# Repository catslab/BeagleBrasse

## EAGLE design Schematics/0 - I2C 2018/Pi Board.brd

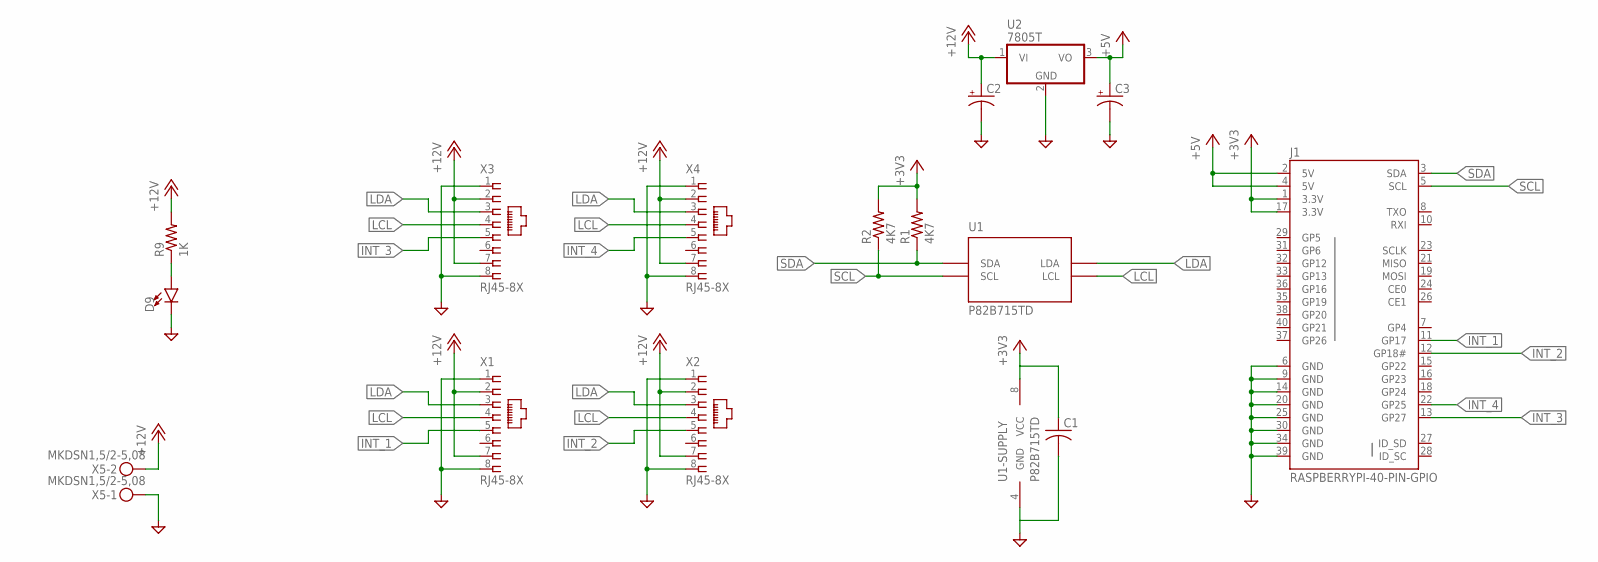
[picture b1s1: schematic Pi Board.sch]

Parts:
C1: C-USC0805; C0805
C2, C3: CPOL-USC; PANASONIC_C
D9: LED3MM; LED_3MM
J1: RASPBERRYPI-40-PIN-GPIO; 2X20-SHROUDED
R1, R2: 4K7; R0805
R9: 1K; R0805
U1: P82B715TD; SOIC-8
U2: 7805T; TO220H
X1, X2, X3, X4: RJ45-8X; RJ45-NO-SHIELD
X5: MKDSN1,5/2-5,08

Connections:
+3V3: C1.1, J1.1 (3.3V), J1.17 (3.3V), R1.2, R2.2, U1.8 (VCC)
+5V: C3.+, J1.2 (5V), J1.4 (5V), U2.3 (VO)
+12VBUS: C2.+, R9.2, U2.1 (VI), X1.2, X1.7, X2.2, X2.7, X3.2, X3.7, X4.2, X4.7, X5.2
DGND: C1.2, C2.-, C3.-, D9.K (C), J1.6 (GND), J1.9 (GND), J1.14 (GND), J1.20 (GND), J1.25 (GND), J1.30 (GND), J1.34 (GND), J1.39 (GND), U1.4 (GND), U2.2 (GND), X1.1, X1.8, X2.1, X2.8, X3.1, X3.8, X4.1, X4.8, X5.1
INT_1: J1.11 (GP17), X1.5
INT_2: J1.12 (GP18#), X2.5
INT_3: J1.13 (GP27), X3.5
INT_4: J1.22 (GP25), X4.5
LCL: U1.2 (LCL), X1.4, X2.4, X3.4, X4.4
LDA: U1.7 (LDA), X1.3, X2.3, X3.3, X4.3
unnamed: D9.A, R9.1
SCL: J1.5 (SCL), R2.1, U1.3 (SCL)
SDA: J1.3 (SDA), R1.1, U1.6 (SDA)

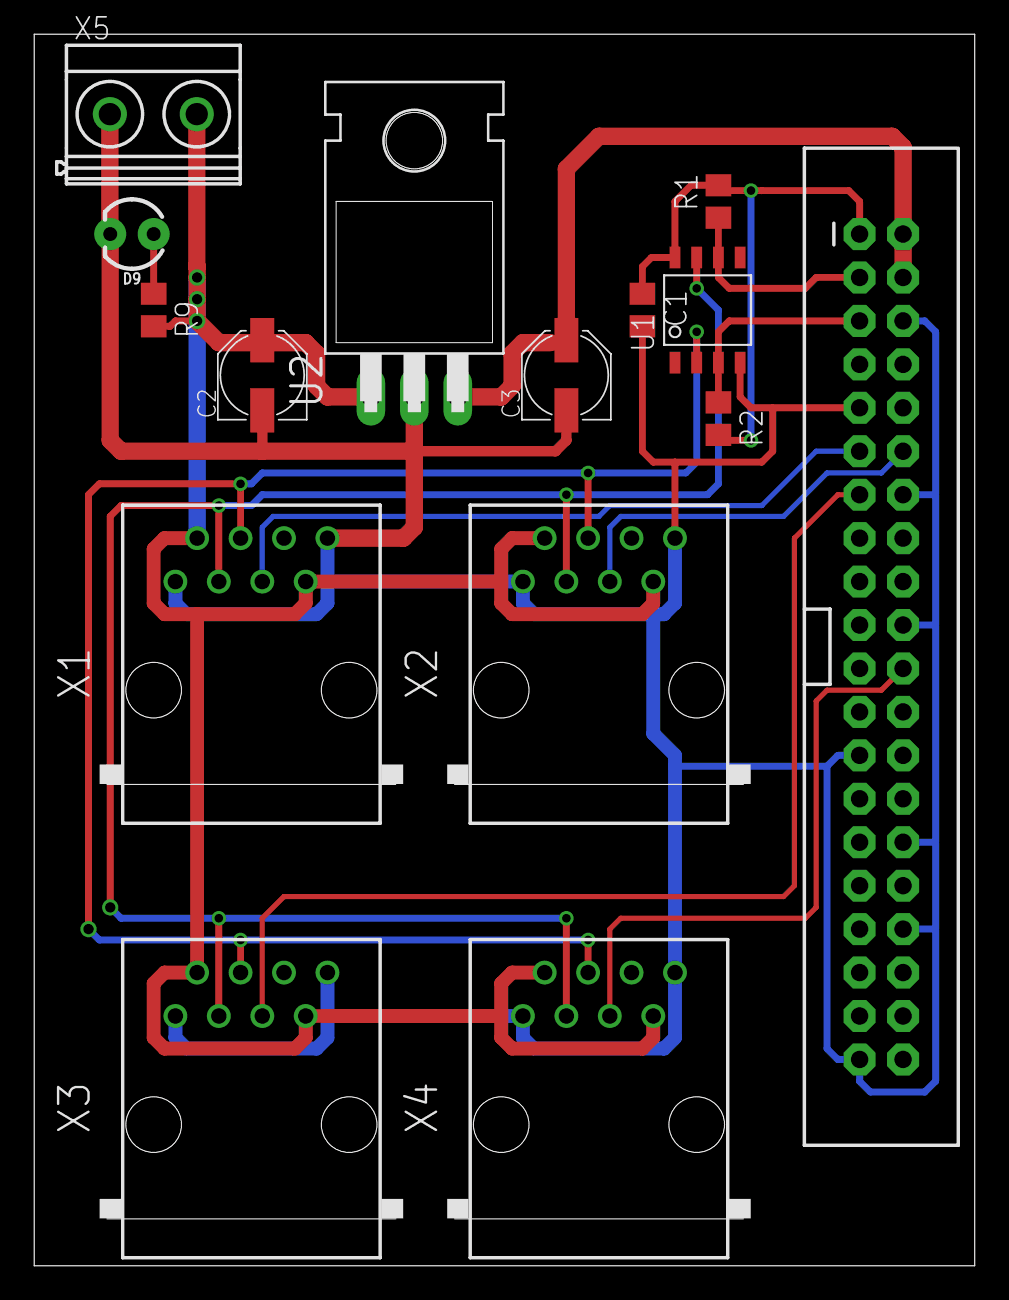
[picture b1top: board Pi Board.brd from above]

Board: 2 copper layers, 55.0 x 72.0 mm, 15 parts (0 on the bottom side), 13 nets.

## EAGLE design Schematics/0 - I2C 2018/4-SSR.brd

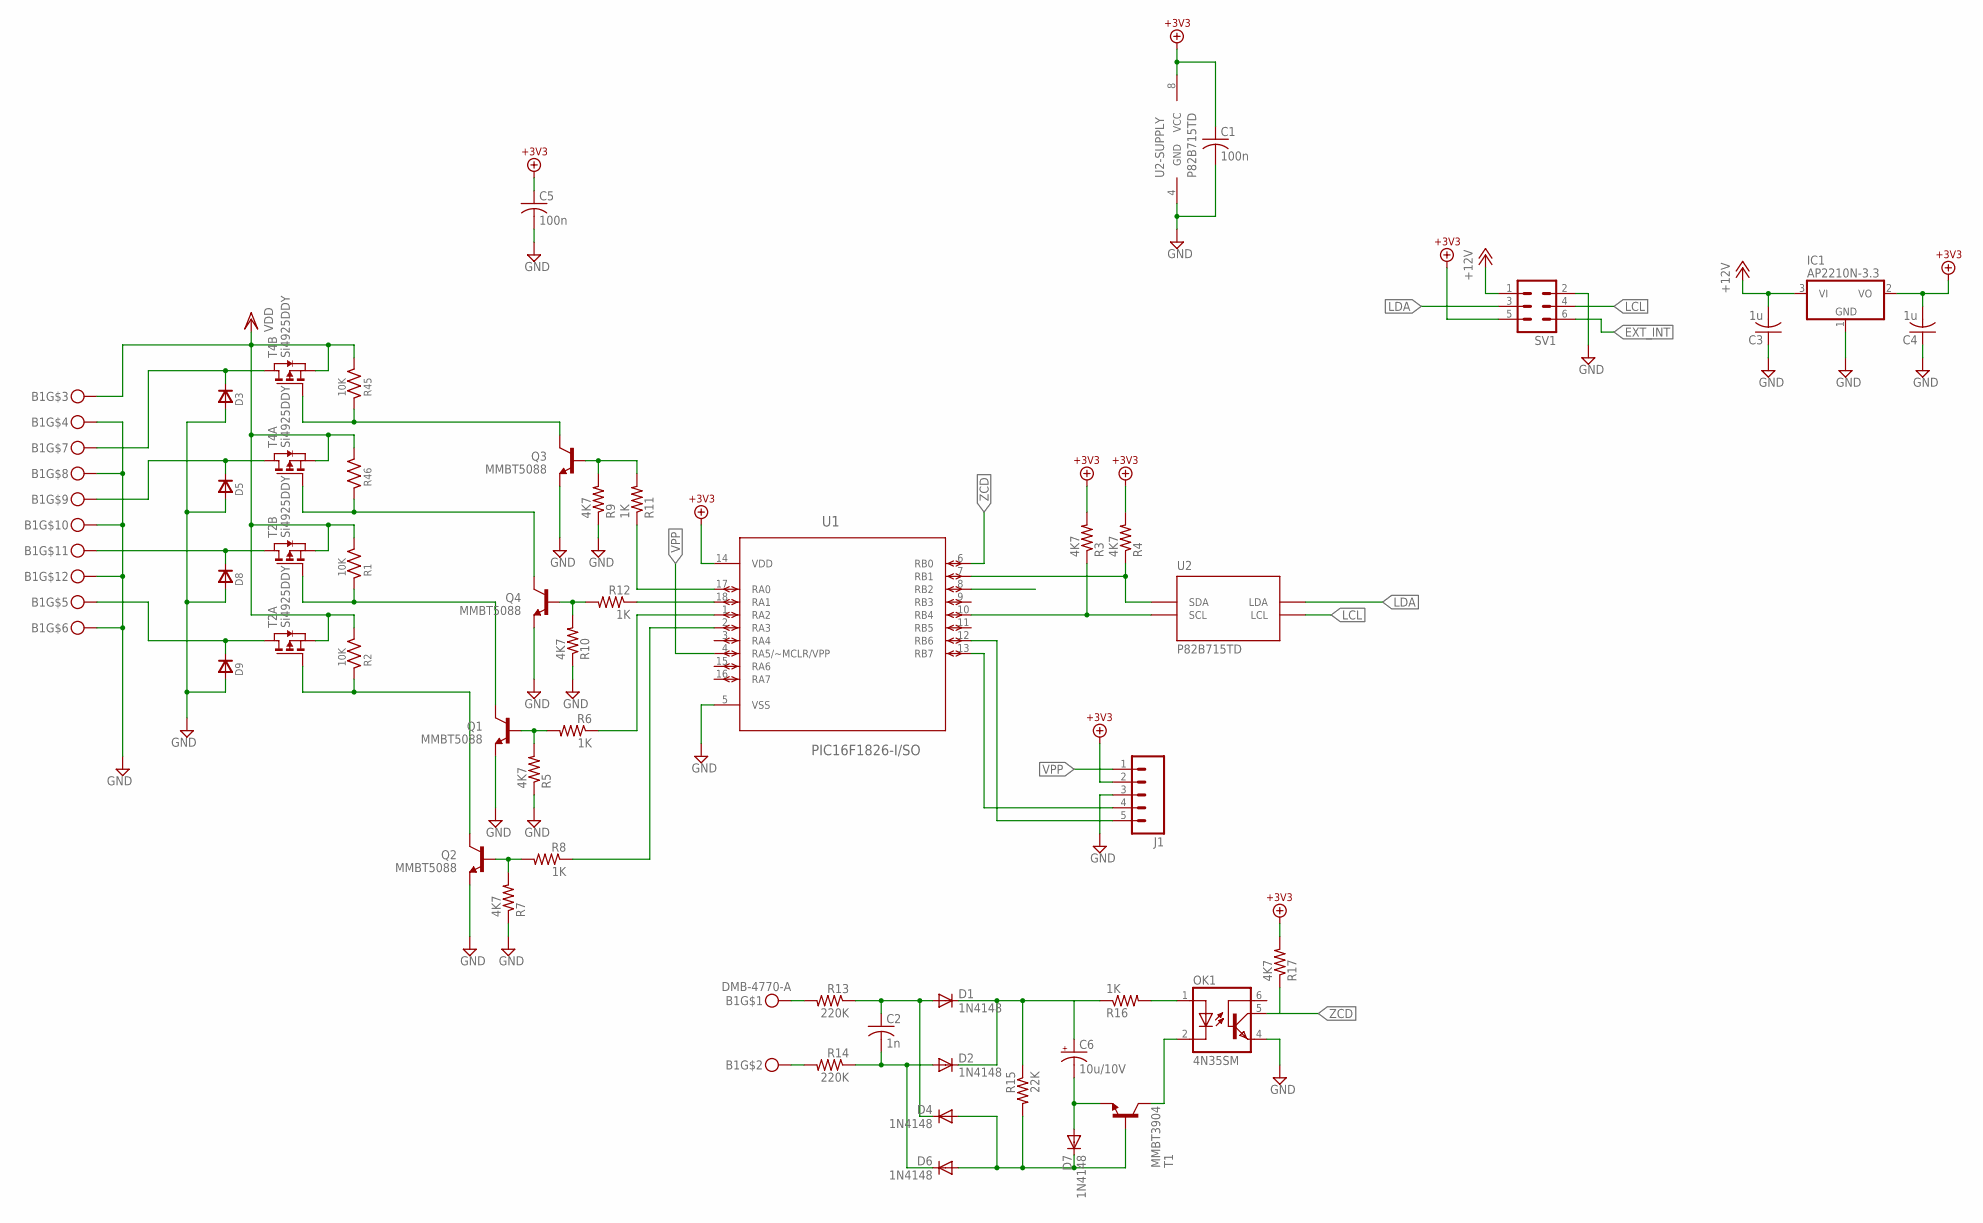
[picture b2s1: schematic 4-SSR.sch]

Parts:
B1: DMB-4770-A; DMB-4770-A-PKG
C1, C5: 100n; C0805
C2: 1n; C1808
C3, C4: 1u; C0805
C6: 10u/10V; PANASONIC_B
D1, D2, D4, D6, D7: 1N4148; SOD80C
D3, D5, D8, D9: DSMA
IC1: AP2210N-3.3; SOT23
J1: M05PTH; 1X05
OK1: 4N35SM; DIL6-SMD
Q1, Q2, Q3, Q4: MMBT5088; SOT23-3
R1, R2, R45: 10K; R0805
R3, R4, R5, R7, R9, R10, R17: 4K7; R0805
R6, R8, R11, R12, R16: 1K; R0805
R13, R14: 220K; R0805
R15: 22K; R0805
R46: RU0805; R0805
SV1: ML6
T1: MMBT3904; SOT23-BEC
T2, T4: Si4925DDY; SO8
U1: PIC16F1826-I/SO; SOIC127P1030X175-18N
U2: P82B715TD; SOIC-8

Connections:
+3V3: C1.1, C4.2, C5.1, IC1.2 (VO), J1.2, R3.2, R4.2, R17.2, SV1.5, U1.14 (VDD), U2.8 (VCC)
+12VBUS: C3.2, IC1.3 (VI), SV1.1
EXT_INT: SV1.6
GND: B1.P$4, B1.P$6, B1.P$8, B1.P$10, B1.P$12, C1.2, C3.1, C4.1, C5.2, D3.A, D5.A, D8.A, D9.A, IC1.1 (GND), J1.3, OK1.4 (EMI), Q1.2 (E), Q2.2 (E), Q3.2 (E), Q4.2 (E), R5.1, R7.1, R9.1, R10.1, SV1.2, U1.5 (VSS), U2.4 (GND)
LCL: SV1.4, U2.2 (LCL)
LDA: SV1.3, U2.7 (LDA)
unnamed: Q1.3 (C), R1.1, T2.4 (G)
unnamed: B1.P$11, D8.C, T2.5 (D), T2.6 (D)
unnamed: Q2.3 (C), R2.1, T2.2 (G)
unnamed: B1.P$5, D9.C, T2.7 (D), T2.8 (D)
unnamed: J1.4, U1.13 (RB7)
unnamed: J1.5, U1.12 (RB6)
unnamed: R12.1, U1.18 (RA1)
unnamed: Q4.3 (C), R46.1, T4.2 (G)
unnamed: Q3.1 (B), R9.2, R11.2
unnamed: R11.1, U1.17 (RA0)
unnamed: Q1.1 (B), R5.2, R6.2
unnamed: Q4.1 (B), R10.2, R12.2
unnamed: B1.P$1, R13.2
unnamed: B1.P$2, R14.2
unnamed: C2.1, D1.A, D4.C, R13.1
unnamed: C2.2, D2.A, D6.C, R14.1
unnamed: C6.+, D1.C, D2.C, R15.1, R16.1
unnamed: C6.-, D7.A, T1.E
unnamed: OK1.1 (A), R16.2
unnamed: D4.A, D6.A, D7.C, R15.2, T1.B
unnamed: OK1.2 (C), T1.C
unnamed: R6.1, U1.1 (RA2)
unnamed: Q2.1 (B), R7.2, R8.2
unnamed: R8.1, U1.2 (RA3)
unnamed: R3.1, U1.10 (RB4), U2.3 (SCL)
unnamed: R4.1, U1.7 (RB1), U2.6 (SDA)
unnamed: Q3.3 (C), R45.1, T4.4 (G)
unnamed: B1.P$7, D3.C, T4.5 (D), T4.6 (D)
unnamed: B1.P$9, D5.C, T4.7 (D), T4.8 (D)
VDD: B1.P$3, R1.2, R2.2, R45.2, R46.2, T2.1 (S), T2.3 (S), T4.1 (S), T4.3 (S)
VPP: J1.1, U1.4 (RA5/~MCLR/VPP)
ZCD: OK1.5 (COL), R17.1, U1.6 (RB0)

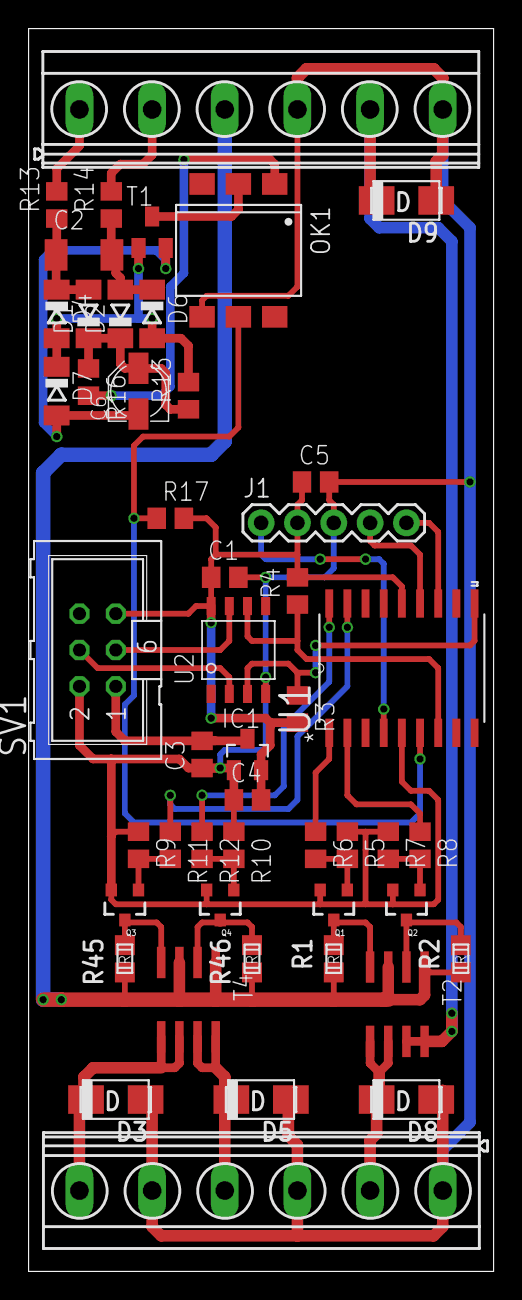
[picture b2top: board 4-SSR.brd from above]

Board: 2 copper layers, 32.5 x 86.9 mm, 48 parts (0 on the bottom side), 37 nets.

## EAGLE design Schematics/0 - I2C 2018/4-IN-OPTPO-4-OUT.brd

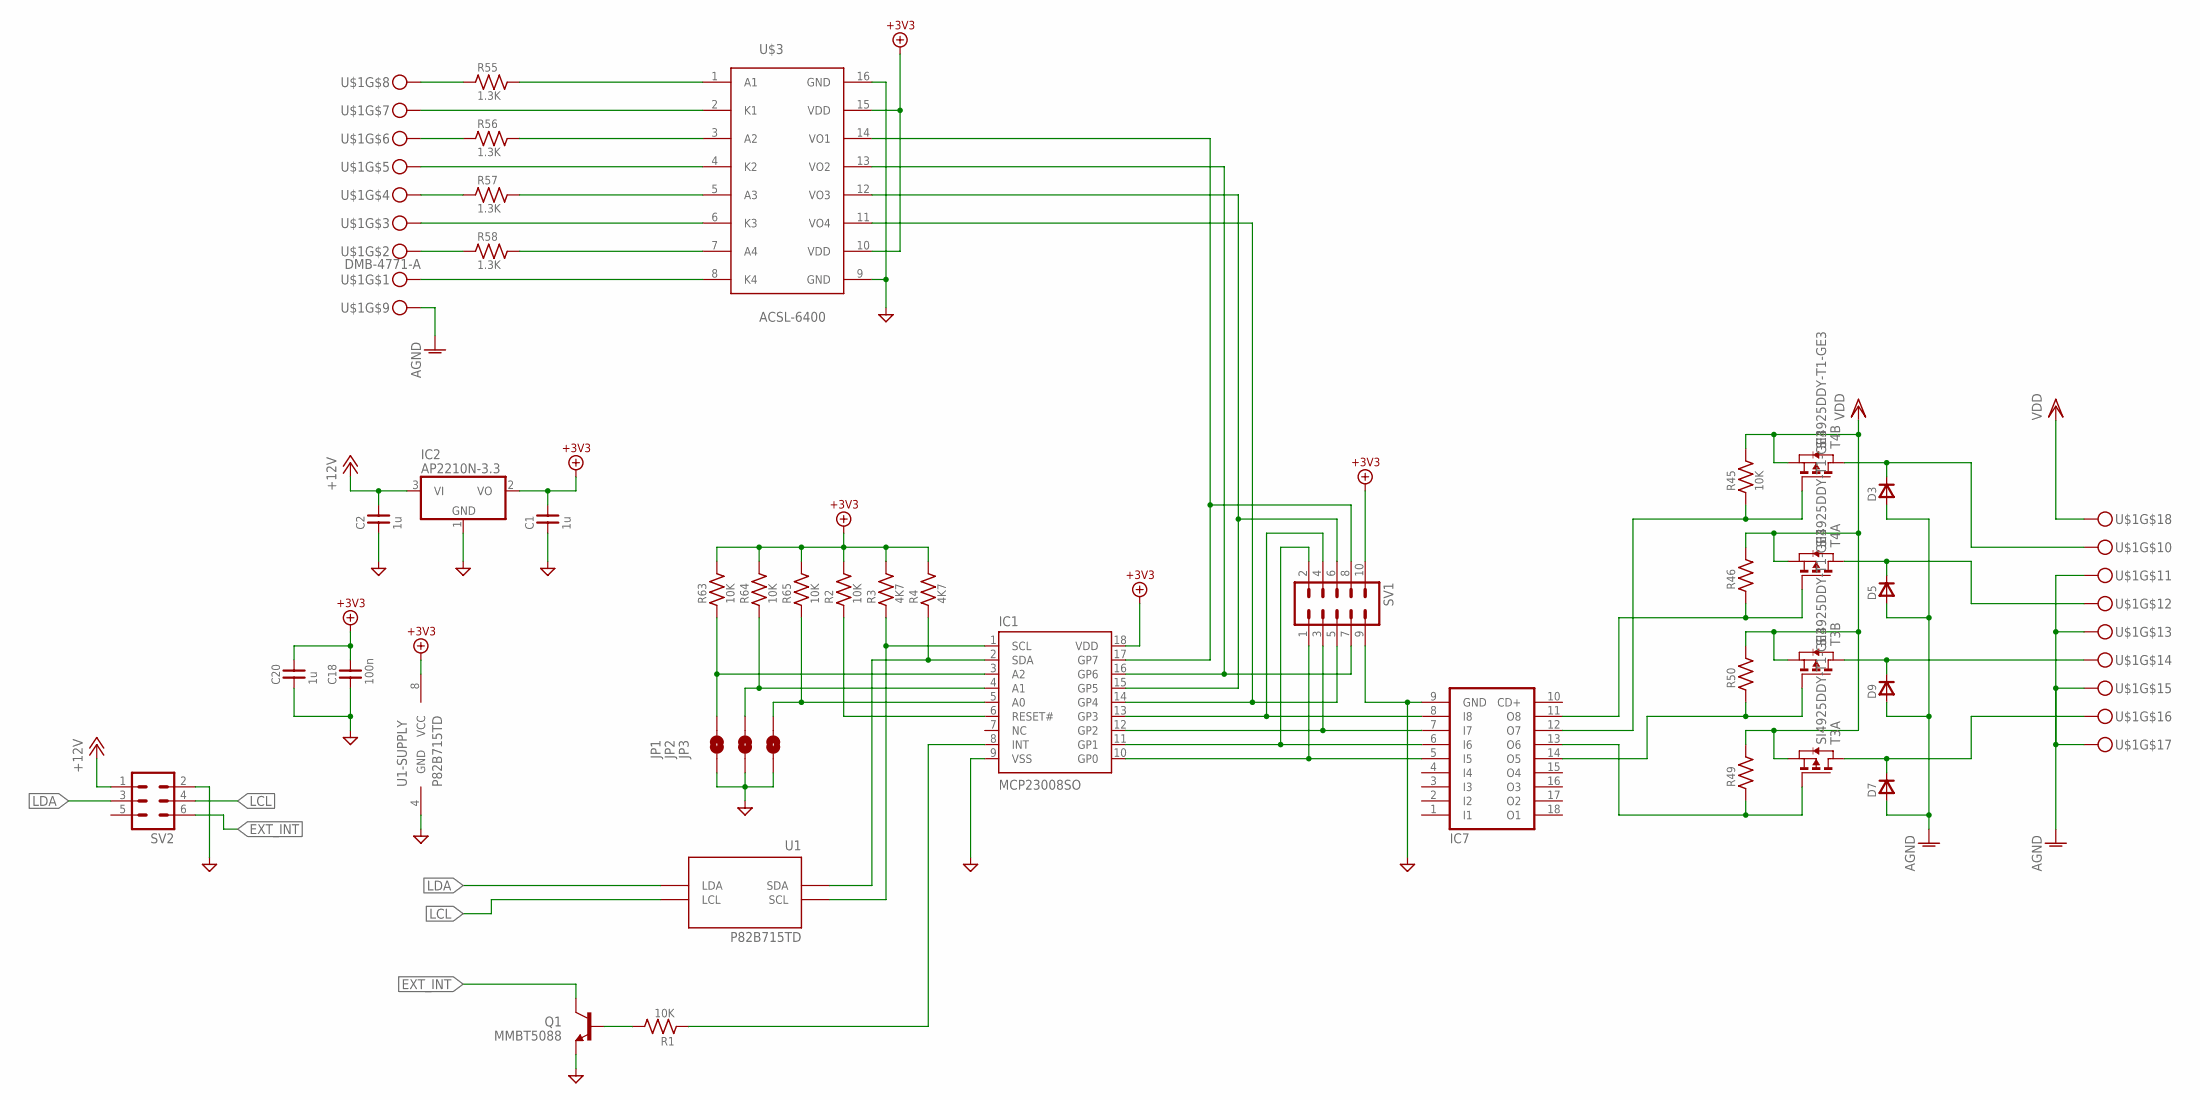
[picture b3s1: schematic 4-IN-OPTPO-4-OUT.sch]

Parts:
C1, C2, C20: 1u; C0805
C18: 100n; C0805
D3, D5, D7, D9: DSMA
IC1: MCP23008SO; SO-18W
IC2: AP2210N-3.3; SOT23
IC7: ULN2803A; SO18W
JP1, JP2, JP3: JUMPER-PAD-2-NOYES_SILK; PAD-JUMPER-2-NO_YES_SILK
Q1: MMBT5088; SOT23-3
R1, R2, R45, R63, R64, R65: 10K; R0805
R3, R4: 4K7; R0805
R46, R49, R50: RU0805; R0805
R55, R56, R57, R58: 1.3K; R0805
SV1: ML10
SV2: ML6
T3, T4: SI4925DDY-T1-GE3; SO8
U1: P82B715TD; SOIC-8
U$1: DMB-4771-A; DMB-4771-A-PKG
U$3: ACSL-6400; SO16

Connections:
+3V3: C1.2, C18.2, C20.2, IC1.18 (VDD), IC2.2 (VO), R2.2, R3.2, R4.2, R63.2, R64.2, R65.2, SV1.10, U1.8 (VCC), U$3.10 (VDD), U$3.15 (VDD)
+12VBUS: C2.2, IC2.3 (VI), SV2.1
AGND: D3.A, D5.A, D7.A, D9.A, U$1.P$9, U$1.P$11, U$1.P$13, U$1.P$15, U$1.P$17
DGND: C1.1, C2.1, C18.1, C20.1, IC1.9 (VSS), IC2.1 (GND), IC7.9 (GND), JP1.1, JP2.1, JP3.1, Q1.2 (E), SV1.9, SV2.2, U1.4 (GND), U$3.9 (GND), U$3.16 (GND)
EXT_INT: Q1.3 (C), SV2.6
LCL: SV2.4, U1.2 (LCL)
LDA: SV2.3, U1.7 (LDA)
unnamed: R55.1, U$1.P$8
unnamed: R56.1, U$1.P$6
unnamed: R57.1, U$1.P$4
unnamed: R58.1, U$1.P$2
unnamed: IC1.13 (GP3), IC7.8 (I8), SV1.4
unnamed: IC1.12 (GP2), IC7.7 (I7), SV1.3
unnamed: IC1.11 (GP1), IC7.6 (I6), SV1.2
unnamed: IC1.10 (GP0), IC7.5 (I5), SV1.1
unnamed: IC1.1 (SCL), R3.1, U1.3 (SCL)
unnamed: IC1.2 (SDA), R4.1, U1.6 (SDA)
unnamed: IC1.8 (INT), R1.1
unnamed: Q1.1 (B), R1.2
unnamed: IC1.6 (RESET#), R2.1
unnamed: IC1.16 (GP6), SV1.7, U$3.13 (VO2)
unnamed: U$1.P$7, U$3.2 (K1)
unnamed: U$1.P$5, U$3.4 (K2)
unnamed: U$1.P$3, U$3.6 (K3)
unnamed: U$1.P$1, U$3.8 (K4)
unnamed: IC7.12 (O7), R45.1, T4.4 (G)
unnamed: IC7.11 (O8), R46.1, T4.2 (G)
unnamed: IC7.13 (O6), R49.1, T3.2 (G)
unnamed: IC7.14 (O5), R50.1, T3.4 (G)
unnamed: D3.C, T4.5 (D), T4.6 (D), U$1.P$10
unnamed: D5.C, T4.7 (D), T4.8 (D), U$1.P$12
unnamed: D7.C, T3.7 (D), T3.8 (D), U$1.P$16
unnamed: D9.C, T3.5 (D), T3.6 (D), U$1.P$14
unnamed: R55.2, U$3.1 (A1)
unnamed: R56.2, U$3.3 (A2)
unnamed: R57.2, U$3.5 (A3)
unnamed: R58.2, U$3.7 (A4)
unnamed: IC1.17 (GP7), SV1.8, U$3.14 (VO1)
unnamed: IC1.15 (GP5), SV1.6, U$3.12 (VO3)
unnamed: IC1.14 (GP4), SV1.5, U$3.11 (VO4)
unnamed: IC1.5 (A0), JP3.2, R65.1
unnamed: IC1.4 (A1), JP2.2, R64.1
unnamed: IC1.3 (A2), JP1.2, R63.1
VDD: R45.2, R46.2, R49.2, R50.2, T3.1 (S), T3.3 (S), T4.1 (S), T4.3 (S), U$1.P$18

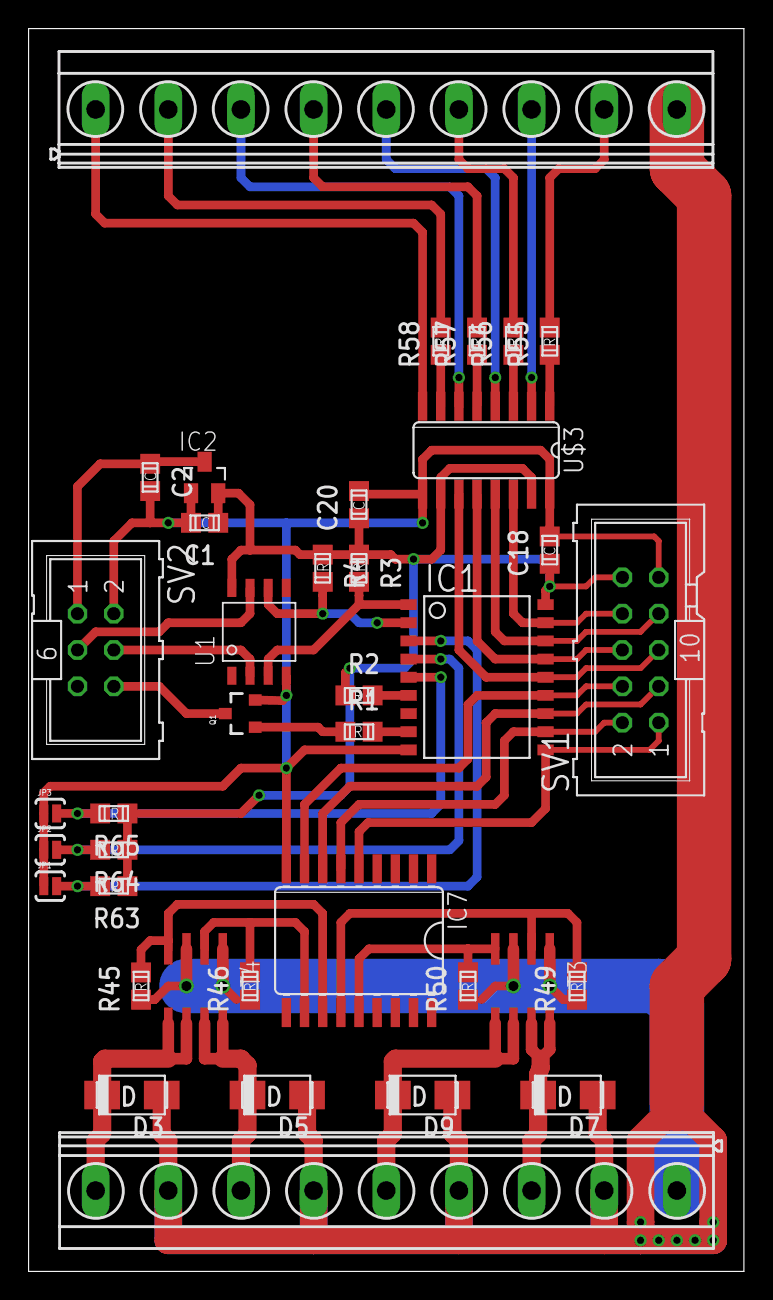
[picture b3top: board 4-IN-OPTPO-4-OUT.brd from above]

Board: 2 copper layers, 50.0 x 86.9 mm, 37 parts (0 on the bottom side), 44 nets.

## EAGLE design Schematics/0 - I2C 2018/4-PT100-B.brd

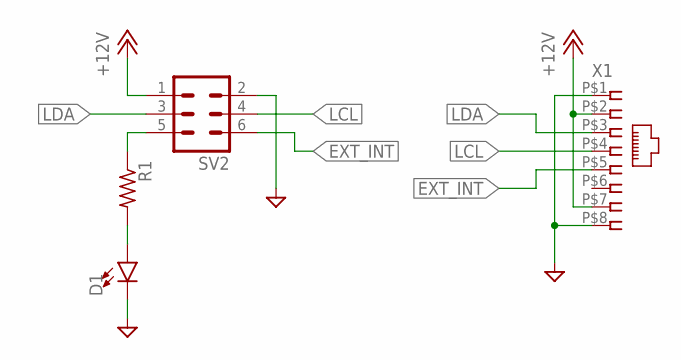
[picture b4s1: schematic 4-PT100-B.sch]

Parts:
D1: LED3MM; LED_3MM
R1: R-US_R0805; R0805
SV2: ML6
X1: RJ45; RJ45-VERT

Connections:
+12VBUS: SV2.1, X1.P$2 (2), X1.P$7 (7)
DGND: D1.K (C), SV2.2, X1.P$1 (1), X1.P$8 (8)
EXT_INT: SV2.6, X1.P$5 (5)
LCL: SV2.4, X1.P$4 (4)
LDA: SV2.3, X1.P$3 (3)
unnamed: D1.A, R1.2
unnamed: R1.1, SV2.5

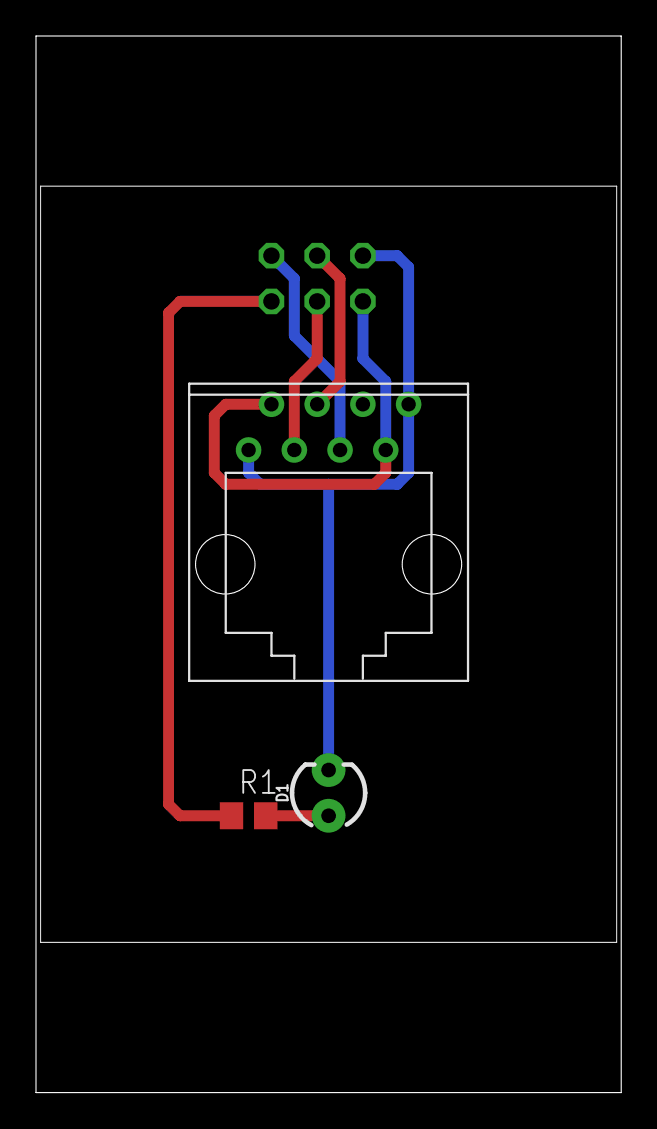
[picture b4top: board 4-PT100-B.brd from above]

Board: 2 copper layers, 32.5 x 58.7 mm, 4 parts (1 on the bottom side), 7 nets.

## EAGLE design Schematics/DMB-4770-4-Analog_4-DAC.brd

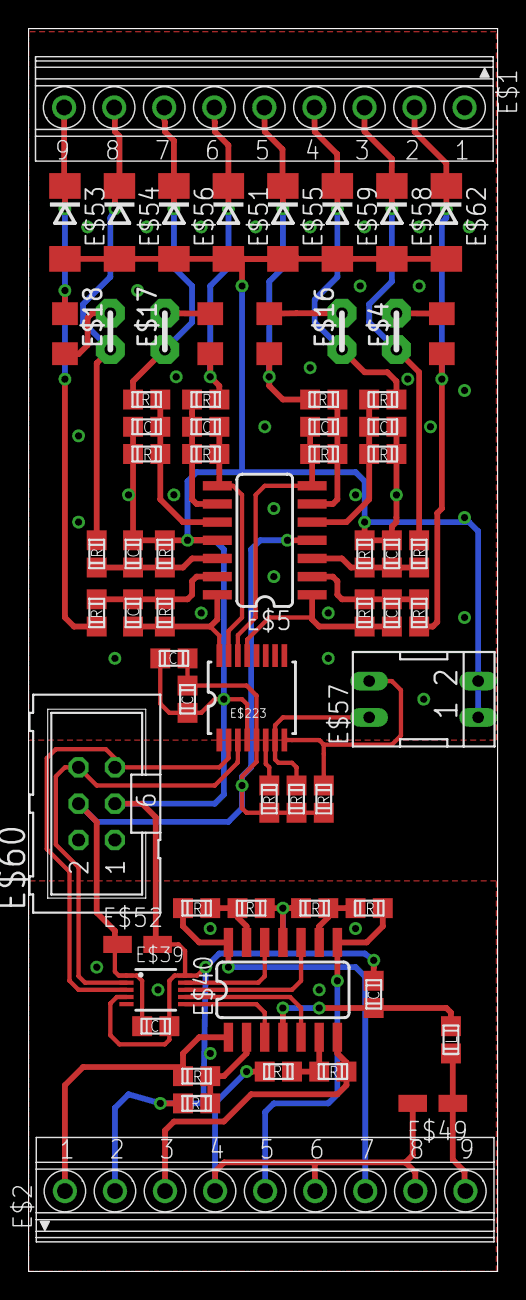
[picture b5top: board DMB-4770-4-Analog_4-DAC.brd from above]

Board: 2 copper layers, 32.8 x 86.9 mm, 66 parts (0 on the bottom side), 45 nets.

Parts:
E$1, E$2: 1751316
E$3, E$10, E$13, E$22, E$24, E$26, E$30, E$32, E$36, E$37, E$38: 100n; C0805
E$4, E$16, E$17, E$18: J01N
E$5: LMV344; SOIC-14
E$6, E$9, E$21, E$23, E$25, E$29, E$31, E$35: 25.5K; R0805
E$7, E$8, E$19, E$66: 500; 1206
E$11, E$12, E$14, E$15, E$27, E$28, E$33, E$34: 102K; R0805
E$39: MCP4728; MSOP10
E$40: OPA4171; SOIC-14
E$41, E$43, E$45, E$46: 82.5K; R0805
E$42, E$44, E$47, E$48: 330K; R0805
E$49, E$52: 10u; CT3216
E$50: 1u; C0805
E$51, E$53, E$55, E$56, E$58, E$59, E$62: 1SMB30AT3G; DO214AA
E$54: DO214AA
E$57: EPG-02
E$60: ML6
E$61: 10uH; L0805
E$223: ADC128D818; TSSOP16
E$224, E$225, E$226: 10K; R0805

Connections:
3V3: E$3.2, E$5.4, E$37.1, E$39.1, E$50.1, E$52.+, E$60.4, E$223.5, E$224.2, E$225.2, E$226.2
GND: E$2.2, E$2.4, E$2.6, E$2.8, E$3.1, E$5.11, E$9.2, E$13.2, E$21.1, E$22.1, E$29.1, E$30.1, E$31.2, E$32.2, E$37.2, E$38.1, E$39.4, E$39.10, E$40.11, E$41.2, E$43.2, E$45.1, E$46.1, E$49.-, E$50.2, E$51.A, E$52.-, E$53.A, E$54.A, E$55.A, E$56.A, E$57.1, E$57.2, E$58.A, E$59.A, E$60.3, E$62.A, E$223.4
IN1+: E$1.8, E$18.1, E$34.2, E$54.C
IN1-: E$1.9, E$33.2, E$53.C, E$66.2
IN2+: E$1.7, E$17.1, E$27.2, E$56.C
IN2-: E$1.6, E$19.2, E$28.2, E$51.C
IN3+: E$1.4, E$15.2, E$16.1, E$59.C
IN3-: E$1.5, E$8.2, E$14.2, E$55.C
IN4+: E$1.3, E$4.1, E$11.2, E$58.C
IN4-: E$1.2, E$7.2, E$12.2, E$62.C
S$8: E$39.3, E$60.5, E$223.2
S$9: E$2.9, E$49.+, E$61.1
S$10: E$4.2, E$7.1
S$11: E$40.6, E$43.1, E$44.1
S$13: E$5.2, E$6.1, E$10.1, E$12.1
S$14: E$5.6, E$14.1, E$23.2, E$24.2
S$15: E$18.2, E$66.1
S$16: E$5.5, E$9.1, E$13.1, E$15.1
S$20: E$17.2, E$19.1
S$21: E$8.1, E$16.2
S$23: E$5.3, E$11.1, E$21.2, E$22.2
S$25: E$5.9, E$25.1, E$26.1, E$28.1
S$28: E$5.12, E$31.1, E$32.1, E$34.1
S$29: E$5.10, E$27.1, E$29.2, E$30.2
S$31: E$39.6, E$40.3
S$32: E$39.7, E$40.5
S$33: E$39.9, E$40.12
S$34: E$39.8, E$40.10
S$35: E$40.2, E$41.1, E$42.2
S$38: E$2.1, E$40.1, E$42.1
S$39: E$2.3, E$40.7, E$44.2
S$40: E$40.13, E$45.2, E$48.2
S$41: E$40.9, E$46.2, E$47.1
S$42: E$2.7, E$40.14, E$48.1
S$47: E$5.8, E$25.2, E$26.2, E$223.15
S$48: E$5.7, E$23.1, E$24.1, E$223.14
S$49: E$5.14, E$35.1, E$36.1, E$223.16
S$50: E$5.1, E$6.2, E$10.2, E$223.13
S$55: E$5.13, E$33.1, E$35.2, E$36.2
S$59: E$2.5, E$40.8, E$47.2
S$231: E$223.6, E$226.1
S$235: E$57.4, E$223.7, E$225.1
S$236: E$57.3, E$223.8, E$224.1
SCL: E$39.2, E$60.6, E$223.3
VCC: E$38.2, E$40.4, E$61.2

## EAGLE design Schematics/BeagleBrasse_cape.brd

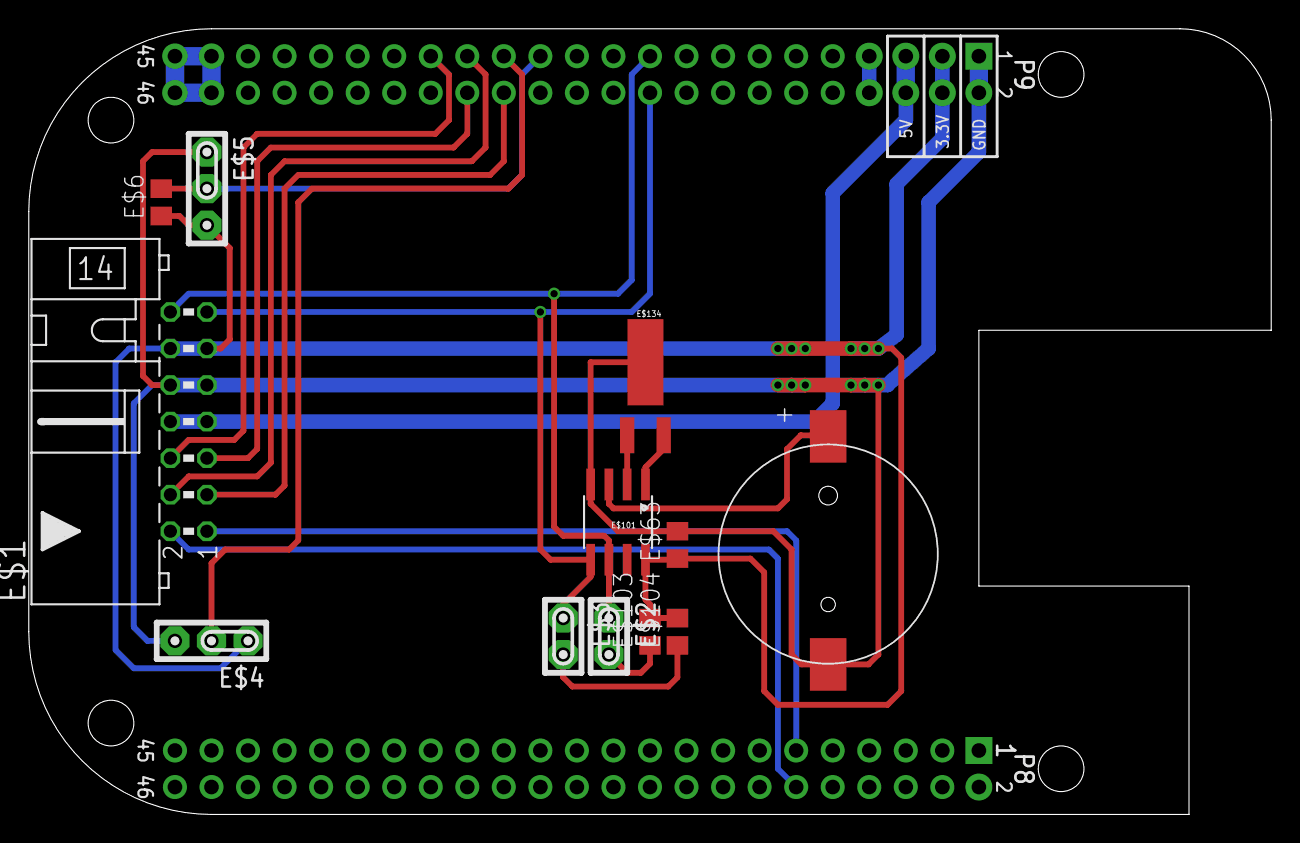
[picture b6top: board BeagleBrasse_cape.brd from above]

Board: 2 copper layers, 86.4 x 54.6 mm, 13 parts (0 on the bottom side), 20 nets.

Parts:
E$1: ML14L
E$2, E$3: JP02N
E$4, E$5: JP03N
E$6, E$103, E$104: 4.7K; C0805
E$63: 0.1; C0805
E$101: DS1338; SOIC8
E$102: BC501SM
E$134: 32.768; CRYSTAL-32KHZ-SMD
U$1: BEAGLE_BONE_BLACK_CAPE

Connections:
S$1: E$1.7, E$1.8, U$1.P9.5, U$1.P9.6
S$2: E$101.2, E$134.X1
S$3: E$101.1, E$134.X2
S$4: E$101.3, E$102.P$2
S$5: E$1.14, E$2.1, E$101.6, U$1.P9.19
S$6: E$1.13, E$3.1, E$101.5, U$1.P9.20
S$7: E$1.3, U$1.P9.28
S$8: E$4.2, U$1.P9.27
S$9: E$3.2, E$104.1
S$10: E$2.2, E$103.1
S$11: U$1.P9.7, U$1.P9.8
S$12: E$5.2, E$6.2, U$1.P9.25
S$13: E$1.5, U$1.P9.30
S$14: E$1.4, U$1.P9.29
S$15: E$1.1, U$1.P8.11
S$16: E$1.2, U$1.P8.12
S$17: E$1.9, E$1.10, E$4.3, E$5.1, E$63.2, E$101.4, E$102.P$1, E$134.SHEILD, U$1.P9.1, U$1.P9.2
S$18: E$1.6, U$1.P9.31
S$19: E$1.11, E$1.12, E$4.1, E$5.3, E$6.1, E$63.1, E$101.8, E$103.2, E$104.2, U$1.P9.3, U$1.P9.4
S$31: U$1.P9.43, U$1.P9.44, U$1.P9.45, U$1.P9.46

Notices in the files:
parts and their libraries:
SparkFun-DiscreteSemi: Licensing: Creative Commons ShareAlike 4.0 International - https://creativecommons.org/licenses/by-sa/4.0
Volks73-NXPSemiconductors: Creative Commons Attribution-ShareAlike 3.0 Unported (CC BY-SA 3.0), http://creativecommons.org/licenses/by-sa/3.0/.
